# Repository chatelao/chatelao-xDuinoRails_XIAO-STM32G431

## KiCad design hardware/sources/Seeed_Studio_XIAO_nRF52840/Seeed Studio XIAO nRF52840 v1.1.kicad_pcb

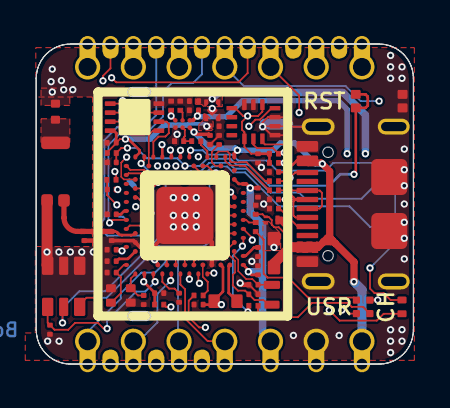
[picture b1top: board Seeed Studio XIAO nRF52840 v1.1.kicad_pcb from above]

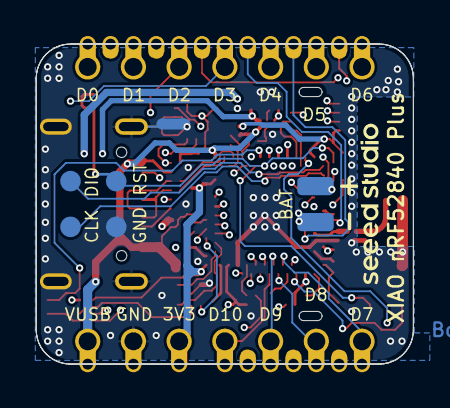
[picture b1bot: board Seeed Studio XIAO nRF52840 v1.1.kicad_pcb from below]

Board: 4 copper layers, 21.0 x 17.8 mm, 68 parts (6 on the bottom side), 73 nets.

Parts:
ANT1: ANTENNA-AN3216; ANT-SMD3P-3.2X1.6X1.04MM
BAT0: TEST-POINT'4080'; TP-80X40MIL
C1, C5, C8, C24, C34: 100nF; C0201
C2, C7: 10pF; C0201
C3, C4, C6, C9, C22, C25, C29, C30, C39, C41, C42: 2.2uF; C0201
C10: 1nF; C0402
C31: 820pF; C0201
C32, C33: 15pF; C0201
C35: 100pF; C0201
C36: 0.8pF; C0201
C37: 0.5pF; C0201
C38: 4.7nH; L0201
C40: DNP; C0201
CHG0: RED; LED-0402
D1: DIODE'0603'; SOD-523
GND0: GND; TP-80X40MIL
K1: BUTTON-4P; SW4-SMD-2.8-2.6X1.6X0.53MM
L3: 10uH; L0603
MIC1: MSM261D3526H1CPM; MIC6P-3.5X2.65X0.94MM
Q1: PMOS_1.00.60.35MM; PMOS_1.0*0.6*0.35MM
R1, R2: 5.1k; R0201
R3, R5, R7: 2.2k; R0201
R4, R13, R14, R15, R20: 10k; R0201
R8: DNP; R0201
R9: 100k; R0201
R10, R11: 33R; R0201
R12, R18: 2.7k; R0201
R16: 1M_1%; R0201
R17: 510k_1%; R0201
RGB6: RGB; 4P1010
TP1, TP2, TP3, TP5: TEST-POINT'4545'; TP-D45MIL
U1: NRF52840_QF; AQFN50P700X700X85_HS-74N
U2: BQ25100; BQ25101_DSBGA_6_BQ25101
U3: LSM6DS3TR-C; LGA14-0.5-2.5X3X0.86MM
U4: XIAO-HALF-HOLE-23P; MOUDLE23P-XIAO-HALF-HOLE
U6: 3.3V; X2SON-4
U7: DNP; USON2X3_8
USB1: USB2.0-TYPE-C
X1: 32.768KHz; X2-SMD-L1.6X1.0X0.5MM
X2: 32MHz; 4P1612

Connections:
/3V3: C3.2, C6.2, C29.2, C39.1, C41.2, R5.1, R13.1, RGB6.+, U1.A22 (VDD@A22), U1.AD14 (VDD@AD14), U1.AD23 (VDD@AD23), U1.B1 (VDD@B1), U1.W1 (VDD@W1), U1.Y2 (VDDH@Y2), U4.12 (3V3), U6.1 (OUT), U7.8 (VCC)
/6D_INT1: U1.T2 (P0.11@T2), U3.4 (INT1)
/6D_PWR: C1.2, R14.1, R15.1, U1.P2 (P1.08@P2), U3.5 (VDDIO), U3.8 (VDD), U3.12 (CS)
/DEC4-6: C34.1, C42.1, L3.2, U1.B5 (DEC4@B5), U1.E24 (DEC6@E24)
/INTERNAL_I2C_SCL: R14.2, U1.H2 (P0.27@H2), U3.13 (SCL)
/INTERNAL_I2C_SDA: R15.2, U1.M2 (P0.07@M2), U3.14 (SDA)
/P0.02_AIN0_LOW_A0_D0: U1.A12 (P0.02/AIN0@A12), U4.1 (PA02_A0_D0)
/P0.03_AIN1_LOW_A1_D1: U1.B13 (P0.03/AIN1@B13), U4.2 (PA4_A1_D1)
/P0.04_AIN2_A4_D4: U1.J1 (P0.04/AIN2@J1), U4.5 (PA8_A4_D4_SDA)
/P0.05_AIN3_A5_D5: U1.K2 (P0.05/AIN3@K2), U4.6 (PA9_A5_D5_SCL)
/P0.06_USER_BLUE: R3.2, U1.L1 (P0.06@L1)
/P0.09/NFC1/RX1: U1.L24 (P0.09/NFC1@L24), U4.18
/P0.10/NFC2/TX1: U1.J24 (P0.10/NFC2@J24), U4.19
/P0.13_HICHG: R12.2, U1.AD8 (P0.13@AD8)
/P0.14_~READ_BAT: R17.2, U1.AC9 (P0.14@AC9)
/P0.15_I2S_SD: U1.AD10 (P0.15@AD10), U4.15
/P0.16_PDM_DATA: MIC1.3 (DATA), U1.AC11 (P0.16@AC11)
/P0.17_~CHG: CHG0.-, R8.1, U1.AD12 (P0.17@AD12), U2.C1 (PRETERM)
/P0.19_I2S_SCK: U1.AC15 (P0.19@AC15), U4.16
/P0.20_QSPI_SIO_0: U1.AD16 (P0.20@AD16), U7.5 (DI)
/P0.21_QSPI_SCK: U1.AC17 (P0.21@AC17), U7.6 (CLK)
/P0.22_QSPI_SIO_2: U1.AD18 (P0.22@AD18), U7.3 (~WP)
/P0.23_QSPI_SIO_3: U1.AC19 (P0.23@AC19), U7.7 (~HOLD)
/P0.24_QSPI_SIO_1: U1.AD20 (P0.24@AD20), U7.2 (DO)
/P0.25_QSPI_CSN: U1.AC21 (P0.25@AC21), U7.1 (~CS)
/P0.26_USER_RED: R7.2, U1.G1 (P0.26@G1)
/P0.28_AIN4_LOW_A2_D2: U1.B11 (P0.28/AIN4@B11), U4.3 (PA10_A2_D2)
/P0.29_AIN5_LOW_A3_D3: U1.A10 (P0.29/AIN5@A10), U4.4 (PA11_A3_D3)
/P0.30_USER_GREEN: R4.2, U1.B9 (P0.30/AIN6@B9)
/P0.31_AIN7_BAT: R16.2, R17.1, U1.A8 (P0.31/AIN7@A8), U4.20
/P1.00_PDM_CLK: MIC1.2 (CLK), U1.AD22 (P1.00@AD22)
/P1.01_I2S_WS: U1.Y23 (P1.01@Y23), U4.17
/P1.03_SCK1: U1.V23 (P1.03@V23), U4.21
/P1.05_MISO1: U1.T23 (P1.05@T23), U4.22
/P1.07_MOSI1: U1.P23 (P1.07@P23), U4.23
/P1.10_MIC_PWR: C8.2, MIC1.1 (VDD), U1.A20 (P1.10@A20)
/P1.11_TX_D6: U1.B19 (P1.11@B19), U4.7 (PB08_A6_D6_TX)
/P1.12_RX_D7: U1.B17 (P1.12@B17), U4.8 (PB09_A7_D7_RX)
/P1.13_SCK_D8: U1.A16 (P1.13@A16), U4.9 (PA7_A8_D8_SCK)
/P1.14_MISO_D9: U1.B15 (P1.14@B15), U4.10 (PA5_A9_D9_MISO)
/P1.15_MOSI_D10: U1.A14 (P1.15@A14), U4.11 (PA6_A10_D10_MOSI)
/RESET: C5.1, K1.1 (A0), K1.3 (A1), R13.2, TP2.T, U1.AC13 (P0.18/RESET@AC13)
/SWDCLK: TP3.T, U1.AA24 (SWDCLK@AA24)
/SWDIO: TP5.T, U1.AC24 (SWDIO@AC24)
/USB_D+: R11.1, USB1.A6 (A6/DP1), USB1.B6 (B6/DP2)
/USB_D-: R10.1, USB1.A7 (A7/DN1), USB1.B7 (B7/DN2)
/VBAT: BAT0.1 (T), C30.1, Q1.1 (D), R16.1, U2.A1 (OUT)
/VBUS: C9.2, C25.2, D1.+, Q1.2 (G), R9.2, U1.AD2 (VBUS@AD2), U2.A2 (IN), U4.14 (5V), USB1.A4_B9 (A4/B9/VBUS), USB1.B4_A9 (B4/A9/VBUS)
/VIN: C4.1, D1.-, Q1.3 (S), U6.3 (EN), U6.4 (IN)
//CE: R20.1, U2.B1 (TS)
GND_POWER: ANT1.2 (GND), C1.1, C2.1, C3.1, C4.2, C5.2, C6.1, C7.1, C8.1, C9.1, C10.2, C22.1, C24.1, C25.1, C29.1, C30.2, C31.2, C32.2, C33.2, C34.2, C35.2, C36.1, C37.1, C39.2, C40.2, C41.1, C42.2, GND0.1 (T), K1.2 (B0), K1.4 (B1), MIC1.4 (GND@1), MIC1.5 (L/R), MIC1.6 (GND@2), R1.2, R2.1, R8.2, R9.1, R18.2, R20.2, TP1.T, U1.B7 (VSS@B7), U1.F23 (VSS_PA@F23), U1.G74 (VSS_PAD), U2.C2 (VSS), U3.1 (SDO/DA0), U3.2 (SDX), U3.3 (SCX), U3.6 (GND@1), U3.7 (GND@2), U4.13 (GND), U6.2 (GND), U6.T (GND), U7.4 (GND), U7.PAD (T), USB1.A1_B12 (A1/B12/GND), USB1.B1_A12 (B1/A12/GND), USB1.S1, USB1.S2, USB1.S3, USB1.S4, USB1.S5 (S1), USB1.S6 (S2), X2.2 (1), X2.4 (3)
unnamed: ANT1.3, C10.1
unnamed: ANT1.1 (S), C37.2, C38.2
unnamed: CHG0.+, R5.2
unnamed: R3.1, RGB6.B-
unnamed: R4.1, RGB6.G-
unnamed: R7.1, RGB6.R-
unnamed: C36.2, C38.1, U1.H23 (ANT@H23)
unnamed: R11.2, U1.AD6 (D+@AD6)
unnamed: R10.2, U1.AD4 (D-@AD4)
unnamed: L3.1, U1.B3 (DCC@B3)
unnamed: C24.2, U1.C1 (DEC1@C1)
unnamed: C40.1, U1.A18 (DEC2@A18)
unnamed: C35.1, U1.D23 (DEC3@D23)
unnamed: C31.1, U1.N24 (DEC5@N24)
unnamed: C22.2, U1.AC5 (DECUSB@AC5)
unnamed: C2.2, U1.D2 (P0.00/XL1@D2), X1.2
unnamed: C7.2, U1.F2 (P0.01/XL2@F2), X1.1
unnamed: C33.1, U1.B24 (XC1@B24), X2.1 (2)
unnamed: C32.1, U1.A23 (XC2@A23), X2.3 (4)
unnamed: R12.1, R18.1, U2.B2 (ISET)
unnamed: R1.1, USB1.A5 (A5/CC1)
unnamed: R2.2, USB1.B5 (B5/CC2)

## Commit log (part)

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2025-11-28 Add schematic for Xiao STM32G431
2025-11-28 Import netlist to KiCad schematic
    Created a python script `hardware/netlist_to_sch.py` to convert a KiCad netlist file (`.net`) into a KiCad schematic file (`.kicad_sch`).
    The script parses the netlist to extract components and their connections, then generates a schematic with embedded symbol definitions.
    Symbols are generated as rectangular boxes with pins, placed in a grid layout.
    Connections are established using wires and net labels attached to pins.
    Generated `hardware/xiao_stm32g431_imported.kicad_sch` from `hardware/xiao_stm32g431.net` as a result.
2025-11-30 Add implementation roadmap for JLCPCB manufacturing
    Added a ROADMAP.md file outlining the steps for schematic design, PCB layout, manufacturing preparation, and ordering at JLCPCB for the XIAO STM32G431 project.
2025-11-30 feat: add XIAO STM32G431 pin mapping documentation
    This commit adds a detailed pinout mapping table (`XIAO_STM32G431_Pinout.md`) for a Seeed Studio XIAO compatible board using the STM32G431CBU6 microcontroller.
    The mapping prioritizes:
    - **Legacy Compatibility:** Matches XIAO RP2040/SAMD21 functions for D0-D10 (Analog, I2C, UART, SPI).
    - **Extended Features:** Exposes SPI2, UART3, and extra Analog inputs via bottom pads.
    - **Robustness:** Avoids BOOT0 (PB8) conflicts on I2C lines by using PA15 for SCL.
2025-11-30 Add Seeed Studio XIAO nRF52840 Plus KiCad files
    Downloaded and extracted the KiCad project files for the Seeed Studio XIAO nRF52840 Plus board into the `seeed/` directory.
    - Source: Seeed Studio Wiki (Seeed_Studio_XIAO_nRF52840_Plus.zip)
    - Files included: .kicad_pro, .kicad_sch, .kicad_pcb, .kicad_prl
2025-11-30 Add partlist and design comparison for XIAO STM32G431
    - Create `hardware/PARTLIST.md` with components derived from netlist.
    - Add "Design Choices & Comparison" section comparing features with XIAO SAMD21 and RP2040.
    - Update `ROADMAP.md` to reference the new partlist.
    - Include RGB LED in partlist to match modern XIAO standards.
2025-11-30 Propose pinout mapping for XIAO STM32G431.
    This proposal outlines the pin assignments for the STM32G431KBU6 on a
    XIAO form factor. It prioritizes compatibility with standard XIAO functions
    (DAC on D0, I2C, SPI, UART) and addresses package constraints (unavailable PB2).
    Key Features:
    - D0 mapped to PA4 for DAC support.
    - Standard interfaces (I2C1, SPI1, USART1) on expected pins.
2025-11-30 Add minimalistic MicroPython build for XIAO STM32G431
    - Create `micropython/` directory with board definition for XIAO_STM32G431.
    - Configure board for 128KB flash (STM32G431KBU6) with minimal features (disabled AsyncIO, Network, etc.).
    - Set up build script `build_firmware.sh` to clone and build MicroPython.
    - Add GitHub Actions workflow `build_micropython.yml` for CI/CD and release publishing.
    - Configure clock to use HSI (16MHz) for system and HSI48 for USB.
2025-11-30 Finalize XIAO STM32G431 Pinout Proposal.
    This update finalizes the pin mapping documentation (`PINOUT_PROPOSAL.md`)
    based on detailed analysis of the STM32G431KBU6 datasheet and user requirements.
    Key Changes:
    - **NeoPixel**: Assigned to PB0 (TIM3_CH3) for PWM/DMA control, replacing discrete RGB LEDs.
    - **Analog**: Comprehensive mapping of COMP and OPAMP peripherals.
    - Correctly identifies OPAMP1 input/output pins to confirm standalone mode capability (VINM on P0/PA3).
2025-11-30 Fix GitHub Actions workflow for MicroPython build
    - Replace broken `resetlabs/setup-arm-none-eabi-gcc` action with `sudo apt-get install gcc-arm-none-eabi`.
    - Upgrade `actions/upload-artifact` to v4 to fix deprecation warning.
    - Upgrade `actions/checkout` to v4.
    - Use `softprops/action-gh-release` instead of deprecated `actions/upload-release-asset`.
2025-12-01 Fix MicroPython build errors and runtime stability - Added missing `stm32g4xx_hal_conf.h` to board directory. - Updated `mpconfigboard.h` to use correct `FLASH_LATENCY_8` for 170MHz clock to prevent 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
2025-12-01 Add Arduino examples for STM32G4 OpAmp, Comparator, and CORDIC
    Added three Arduino sketches in `software/examples/` demonstrating advanced hardware features of the STM32G431:
    1. `STM32G4_OpAmp_Buffer`: Configures internal OpAmp1 as a voltage follower (D2 -> D3).
    2. `STM32G4_Comparator_DAC`: Configures internal COMP1 with DAC1 reference (D2 vs 1.65V -> D9).
    3. `STM32G4_CORDIC_SinCos`: Demonstrates CORDIC hardware accelerator for high-speed trigonometry.
2025-12-01 Add AGENTS.md with roadmap instructions
    Added AGENTS.md to the root directory with instructions for agents to:
    1. Read ROADMAP.md before every task.
    2. Update ROADMAP.md at the end of every task.
2025-12-01 Add reference designs for XIAO and QT Py boards
    Created `hardware/sources` and added:
    - Seeed Studio XIAO nRF52840 (KiCad files copied from `seeed/`)
    - Seeed Studio XIAO Expansion Board (Eagle files downloaded from Wiki)
    - Adafruit QT Py RP2040 (Eagle/KiCad files cloned from GitHub)
    These examples serve as references for the XIAO STM32G431 design.
2025-12-01 Fix MicroPython build for 128KB STM32G431
    - Explicitly disable floating point support in mpconfigboard.h and mpconfigboard.mk
    - Create minimal manifest.py to exclude standard frozen modules (e.g. dht) that require floats
    - Update build configuration to ensure firmware fits in 128KB flash
    - Fix linker script usage and HAL configuration paths
2025-12-01 Add documentation index with manuals and application notes
    Created DOCUMENTATION.md containing links to:
    - Official STM32G431 Datasheet, Reference Manual (RM0440), and Errata (ES0431).
    - Application notes for Analog features (OpAmp, Comparator, DAC).
    - Application notes for Coprocessors (CORDIC, FMAC).
2025-12-01 Fix MicroPython build errors by updating linker script and disabling unused features
    - Changed `mpconfigboard.mk` to use `boards/common.ld` instead of `boards/common_basic.ld` which does not exist.
    - Updated `mpconfigboard.h` to disable `MICROPY_HW_ENABLE_INTERNAL_FLASH_STORAGE` to prevent linker errors on 128KB flash.
    - Explicitly disabled `MICROPY_PY_MACHINE_IDLE` and `MICROPY_PY_LWIP` to resolve "used but never defined" errors in `modmachine.c`.
    - Confirmed minimal build settings for STM32G431KBU6 (128KB Flash).
2025-12-01 Fix MicroPython build errors by undefining unused machine features and adding pins.csv
    - Explicitly `#undef` `MICROPY_PY_MACHINE_IDLE`, `MICROPY_PY_MACHINE_PULSE`, and `MICROPY_PY_LWIP` in `mpconfigboard.h` before setting them to 0. This resolves the "used but never defined" compilatio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
    - Added `pins.csv` mapping standard XIAO pins (D0-D10) and system pins (USB, SWD, LED) for the STM32G431.
    - Ensured `manifest.py` is present (empty) to avoid freezing modules that require floats.
    - Confirmed minimal build settings for 128KB Flash target.
2025-12-02 Fix netlist to align with Pinout Proposal and Standard XIAO Layout
    - Update `hardware/xiao_stm32g431.net`:
    - Re-map U1 (STM32G431KBU6) pins to match `XIAO_STM32G431_Pinout.md` as closely as possible within 32-pin constraints.
    - D0=PA4, D1=PA0, D2=PA1, D3=PA2.
    - Correct PA15 assignment (Pin 25).
    - Reorder J3 header pins to match Standard XIAO (5V, GND, 3V3, D10, D9, D8, D7).
    - Map D10 to PA7 and connect to J3 Pin 4.
2025-12-02 Fix MicroPython build: Enable MACHINE_IDLE correctly
    Updated mpconfigboard.h and mpconfigboard.mk to explicitly disable
    MICROPY_PY_MACHINE_IDLE via CFLAGS to resolve the "used but never defined"
    error in modmachine.c. Provided build scripts and workflows.
2025-12-02 Fix MicroPython build: Correctly disable MACHINE_IDLE
    Restored `MICROPY_PY_MACHINE_IDLE = 0` as a Make variable in `mpconfigboard.mk`
    alongside the `CFLAGS` override. This ensures the build system correctly
    generates the flags to disable the idle function, preventing the
    "used but never defined" compilation error. Verified pin mappings against
    project netlist.
2025-12-06 Add STM32G4 FMAC and CORDIC examples
    Added two new Arduino sketches to the `software/examples` directory:
    - `STM32G4_FMAC_FIR`: Demonstrates using the FMAC peripheral for a 7-tap FIR filter in polling mode.
    - `STM32G4_CORDIC_Polar`: Demonstrates using the CORDIC peripheral for Cartesian-to-Polar conversion (Modulus/Phase).
    Verified FMAC HAL usage against the stm32g4xx_hal_driver headers.
2025-12-06 Add GitHub Actions workflow for Arduino builds
    Created .github/workflows/arduino_build.yml to:
    - Compile all sketches in software/examples/ on every push.
    - Use STM32duino Core with Generic G431KBUx configuration.
    - Publish compiled .hex files as artifacts on every build.
    - Upload .hex files to Release assets when a release is published.
2025-12-06 Update GitHub Actions to v4 to fix deprecation error
    Updated actions/checkout and actions/upload-artifact to v4 in .github/workflows/arduino_build.yml.
    This resolves the build failure caused by the deprecation of node16 runtime in v3 actions.
2025-12-06 Fix Arduino build by enabling HAL modules and correcting CORDIC scaling
    - Added `hal_conf_extra.h` to all example sketches to explicitly enable required HAL modules (CORDIC, FMAC, OPAMP, COMP, DAC) which are disabled by default in Generic STM32G4 variants.
    - Fixed CORDIC Polar example to use a smaller input radius (0.5 instead of 0.8) to prevent q1.31 overflow caused by the CORDIC algorithm's intrinsic gain (~1.647).
2025-12-06 Add STM32G4 FMAC FIR and CORDIC Polar Arduino examples
    This commit adds two new Arduino examples to the software/examples directory:
    1. STM32G4_FMAC_FIR: Demonstrates how to use the FMAC hardware accelerator for FIR filtering in polling mode using q1.15 fixed-point format.
    2. STM32G4_CORDIC_Polar: Demonstrates how to use the CORDIC hardware accelerator for Rectangular-to-Polar conversion, including necessary scaling to handle the intrinsic gain of the Modulus function.
    These examples complement the existing OpAmp, Comparator/DAC, and CORDIC SinCos examples.
2025-12-06 Add GitHub Actions workflow for Arduino builds
    This commit adds a new GitHub Actions workflow `.github/workflows/arduino_build.yml` to automatically compile the Arduino examples on every push to any branch and on pull requests.
    The workflow:
    - Installs Arduino CLI and the STM32 core.
    - Compiles all sketches in `software/examples/` using the FQBN `STMicroelectronics:stm32:GenG4:pnum=GENERIC_G431KBUX,usb=CDCgen`.
    This ensures that all examples remain compatible with the STM32G4 configuration.
    Also updated `ROADMAP.md` to reflect the addition of CI/CD.
2025-12-06 Add hal_conf_extra.h to enable HAL modules in Arduino examples
    This commit fixes build errors in the Arduino examples caused by missing HAL module definitions.
    The STM32duino core does not enable all HAL modules (CORDIC, FMAC, OpAmp, DAC, COMP) by default to save flash.
    We add `hal_conf_extra.h` to each example directory to explicitly enable the required modules:
    - STM32G4_CORDIC_Polar: Enables CORDIC
    - STM32G4_CORDIC_SinCos: Enables CORDIC
    - STM32G4_FMAC_FIR: Enables FMAC
2025-12-07 Finalize Arduino examples and CI with build fixes
    This commit bundles the following changes:
    - New `STM32G4_FMAC_FIR` and `STM32G4_CORDIC_Polar` examples.
    - New `.github/workflows/arduino_build.yml` for CI.
    - `hal_conf_extra.h` files added to all examples to enable required HAL modules.
    - Updated `ROADMAP.md`.
    This ensures the repository has a working set of advanced hardware examples and a CI pipeline to verify them.
